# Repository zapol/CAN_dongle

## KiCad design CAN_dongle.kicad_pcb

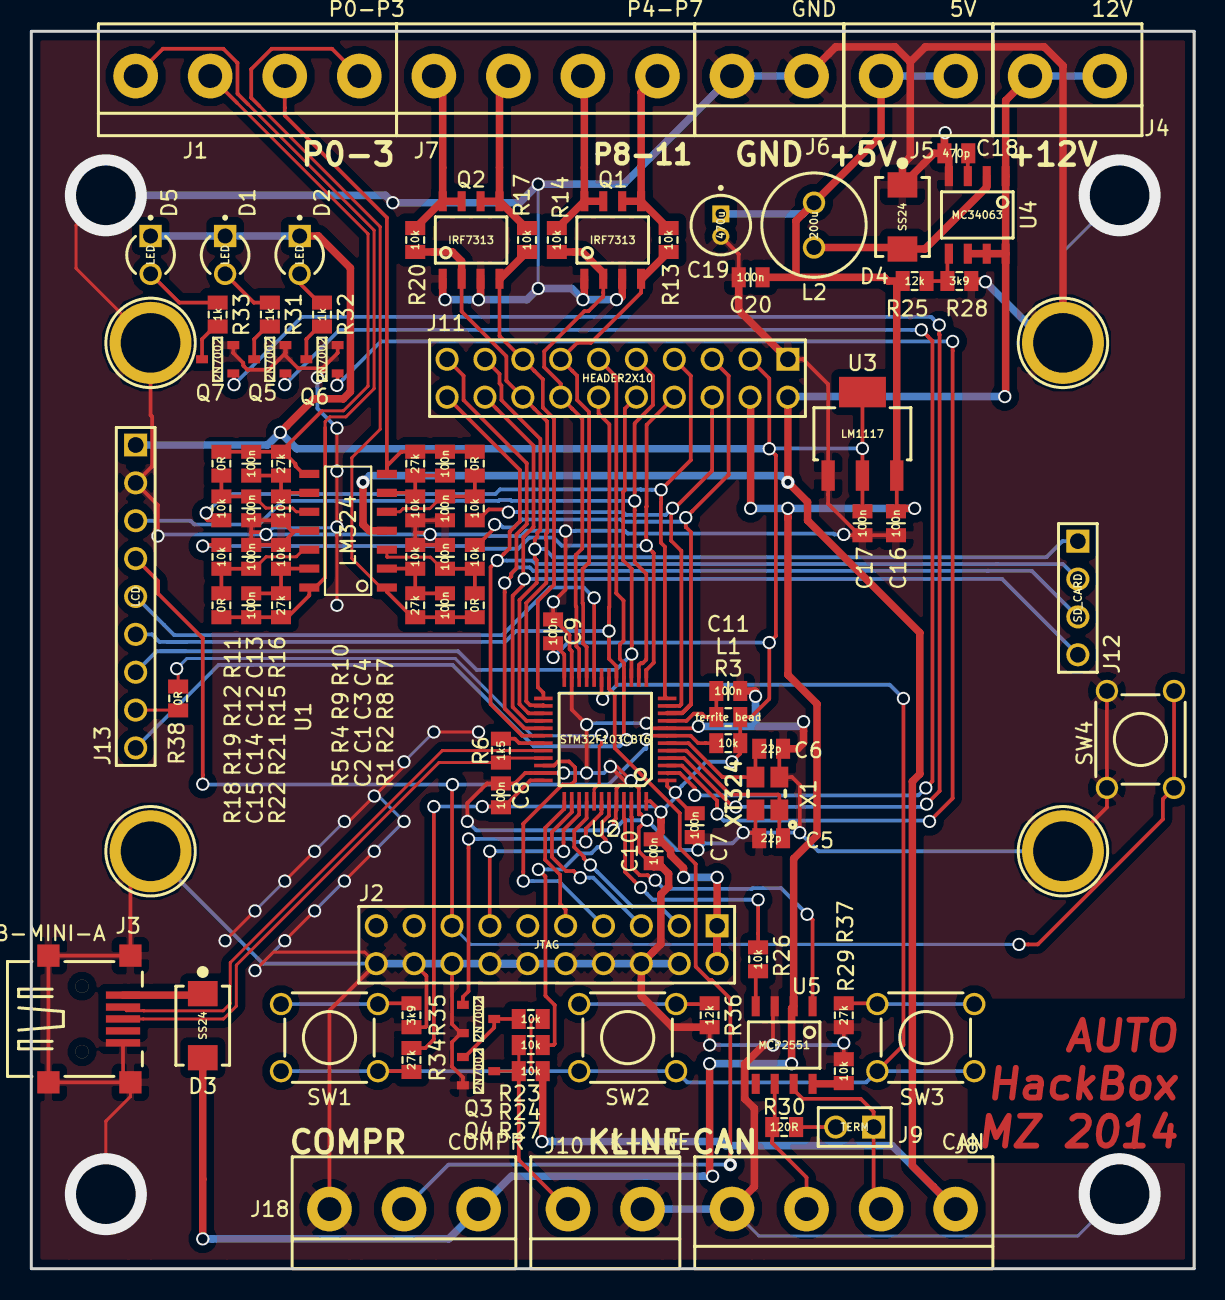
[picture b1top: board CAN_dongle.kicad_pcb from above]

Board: 2 copper layers, 78.0 x 83.0 mm, 100 parts (0 on the bottom side), 80 nets.

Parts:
C1, C2, C3, C4, C7, C8, C9, C10, C11, C12, C13, C14, C15, C16, C17, C20: 100n; C0805
C5, C6: 22p; C0805
C18: 470p; C0805
C19: 470u; CAPPR_P15D40
D1, D2, D5: LED; LED_3MM
D3, D4: SS24; SMB
J1: P0-P3; AK306_LE-4
J2: JTAG; HEADER2x10V
J3: USB-MINI-A; USB-A-MINI
J4: 12V; AK306_LE-2
J5: 5V; AK306_LE-2
J6: GND; AK306_LE-2
J7: P4-P7; AK306_LE-4
J8: CAN; AK306_LE-4
J9: TERM; HEADER1x2V
J10: K-LINE; AK306_LE-2
J11: HEADER2X10; HEADER2x10V
J12: SD_CARD; HEADER1x4V
J13: LCD; HEADER1x9V
J14, J15, J16, J17: LCD_MNTHOLE; MountHole_D4P6
J18: COMPR; AK306_LE-3
L1: ferrite bead; R0805
L2: 200u; INDRD_P30D70
Q1, Q2: IRF7313; SO8_L
Q3, Q4, Q5, Q6, Q7: 2N7002; SOT23
R1, R7, R11, R18, R38: 0R; R0805
R2, R3, R4, R8, R9, R12, R13, R14, R15, R17, R19, R20, R21, R23, R24, R26, R27, R29: 10k; R0805
R5, R10, R16, R22, R34, R37: 27k; R0805
R6: 1k5; R0805
R25, R36: 12k; R0805
R28, R35: 3k9; R0805
R30: 120R; R0805
R31, R32, R33: 1k; R0805
SW1, SW2, SW3, SW4: SWITCH_DUALPINS; TACT_SWITCH_TH_5MM
U1: LM324; SO14
U2: STM32F103CBT6; LQFP48_L
U3: LM1117; SOT223
U4: MC34063; SO8_L
U5: MCP2551; SO8_L
X1: XT324

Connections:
+3V3: C7.2, C8.2, C9.2, C10.2, C17.2, D1.1, D2.1, D5.1, J2.1, J2.2, J11.3, J13.1, L1.1, R3.1, R34.1, U2.1, U2.24, U2.36, U2.48, U3.2, U3.4
+5V: C16.2, C19.1, C20.1, D3.2, J5.1, J5.2, J11.4, J18.1, L2.2, R25.2, U3.3, U5.2
+12V: J4.1, J4.2, J8.1, J11.2, R23.2, R24.2, U1.4, U4.1, U4.6, U4.7, U4.8
/BUTTONS: R34.2, SW1.3, SW1.4, SW2.3, SW2.4, SW3.3, SW3.4, U2.19
/CANH: J8.2, J9.1, U5.7
/CANL: J8.3, R30.1, U5.6
/CANRX: R26.1, U2.45
/CANTX: U2.46, U5.1
/COMPRESSION: J18.2, U2.18
/K-LINE: J10.2, Q4.3, R24.1, R27.2
/LCD_D/C: J13.5, U2.20
/LCD_LED: R38.2, U2.41
/NJTRST: J2.3, U2.40
/NRST: J2.15, J13.4, R3.2, SW4.3, SW4.4, U2.7
/P0: J11.5, R2.1, U2.10
/P1: J11.6, R8.1, U2.11
/P2: J11.7, R12.1, U2.12
/P3: J11.8, R19.1, U2.13
/P4: J11.9, J13.3, U2.14
/P5: J11.10, J13.7, U2.15
/P6: J11.11, J13.9, U2.16
/P7: J11.12, J13.6, U2.17
/P8: J11.13, Q1.4, R13.1, U2.21
/P9: J11.14, Q1.2, R14.1, U2.22
/P10: J11.15, Q2.4, R17.1, U2.25
/P11: J11.16, Q2.2, R20.1, U2.26
/P12: J11.17, J12.1, U2.27
/P13: J11.18, J12.4, U2.28
/P14: J11.19, J12.3, U2.29
/P15: J11.20, J12.2, U2.30
/RxD: R27.1, U2.43
/TCK: J2.9, U2.37
/TDI: J2.5, U2.38
/TDO: J2.13, U2.39
/TMS: J2.7, U2.34
/TxD: Q3.1, U2.42
/USB_DM: J3.2, U2.32
/USB_DP: J3.3, R6.1, U2.33
/USB_EN: R6.2, U2.31
GND: C1.1, C3.1, C5.1, C6.1, C7.1, C8.1, C9.1, C10.1, C11.1, C12.1, C14.1, C16.1, C17.1, C18.1, C19.2, C20.2, D4.1, J2.4, J2.6, J2.8, J2.10, J2.12, J2.14, J2.16, J2.18, J2.20, J3.5, J3.6, J3.7, J3.8, J3.9, J6.1, J6.2, J8.4, J10.1, J11.1, J13.2, J14.1, J15.1, J16.1, J17.1, J18.3, Q1.1, Q1.3, Q2.1, Q2.3, Q3.2, Q4.2, Q5.2, Q6.2, Q7.2, R4.1, R9.1, R15.1, R21.1, R28.1, R29.1, R35.2, R36.2, R37.2, SW4.1, SW4.2, U1.11, U2.8, U2.23, U2.35, U2.44, U2.47, U3.1, U4.4, U5.3, X1.2, X1.4
unnamed: C1.2, R1.1, R2.2, U1.3
unnamed: C2.1, R4.2, R5.1, U1.2
unnamed: C2.2, J1.1, R1.2, R5.2, U1.1
unnamed: C3.2, R7.1, R8.2, U1.5
unnamed: C4.1, R9.2, R10.1, U1.6
unnamed: C4.2, J1.2, R7.2, R10.2, U1.7
unnamed: C5.2, U2.5, X1.1
unnamed: C6.2, U2.6, X1.3
unnamed: C11.2, L1.2, U2.9
unnamed: C12.2, R11.1, R12.2, U1.10
unnamed: C13.1, R15.2, R16.1, U1.9
unnamed: C13.2, J1.3, R11.2, R16.2, U1.8
unnamed: C14.2, R18.1, R19.2, U1.12
unnamed: C15.1, R21.2, R22.1, U1.13
unnamed: C15.2, J1.4, R18.2, R22.2, U1.14
unnamed: C18.2, U4.3
unnamed: D1.2, R31.1
unnamed: D2.2, R32.1
unnamed: D3.1, J3.1
unnamed: D4.2, L2.1, U4.2
unnamed: D5.2, R33.1
unnamed: J7.1, Q1.5, Q1.6, R13.2
unnamed: J7.2, Q1.7, Q1.8, R14.2
unnamed: J7.3, Q2.5, Q2.6, R17.2
unnamed: J7.4, Q2.7, Q2.8, R20.2
unnamed: J9.2, R30.2
unnamed: J13.8, R38.1
unnamed: Q3.3, Q4.1, R23.1
unnamed: Q5.1, U2.2
unnamed: Q5.3, R31.2
unnamed: Q6.1, U2.3
unnamed: Q6.3, R32.2
unnamed: Q7.1, U2.4
unnamed: Q7.3, R33.2
unnamed: R25.1, R28.2, U4.5
unnamed: R26.2, U5.4
unnamed: R29.2, U5.8
unnamed: R35.1, SW1.1, SW1.2
unnamed: R36.1, SW2.1, SW2.2
unnamed: R37.1, SW3.1, SW3.2

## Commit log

2014-06-17 Schematic - work in progress
2014-06-18 Finished Schematic, started component placement
2014-07-31 Added LCD, buttons, remapped pins
2014-07-31 Added calculator for ADC buttons. Added input for compression meter. First placement done.
2014-08-01 Finished first routing. Could be packed more. Verify LCD connectors placement. Reduce via sizes.
2014-08-01 Some optimisations. Moved LEDs to upper part of the board
2014-08-01 Added copper planes. Added some GND vias
2014-08-08 Added mounting holes. Placed references ando other silkscreen texts.
